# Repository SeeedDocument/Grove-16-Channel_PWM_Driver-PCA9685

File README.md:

# Grove-16-Channel_PWM_Driver-PCA9685

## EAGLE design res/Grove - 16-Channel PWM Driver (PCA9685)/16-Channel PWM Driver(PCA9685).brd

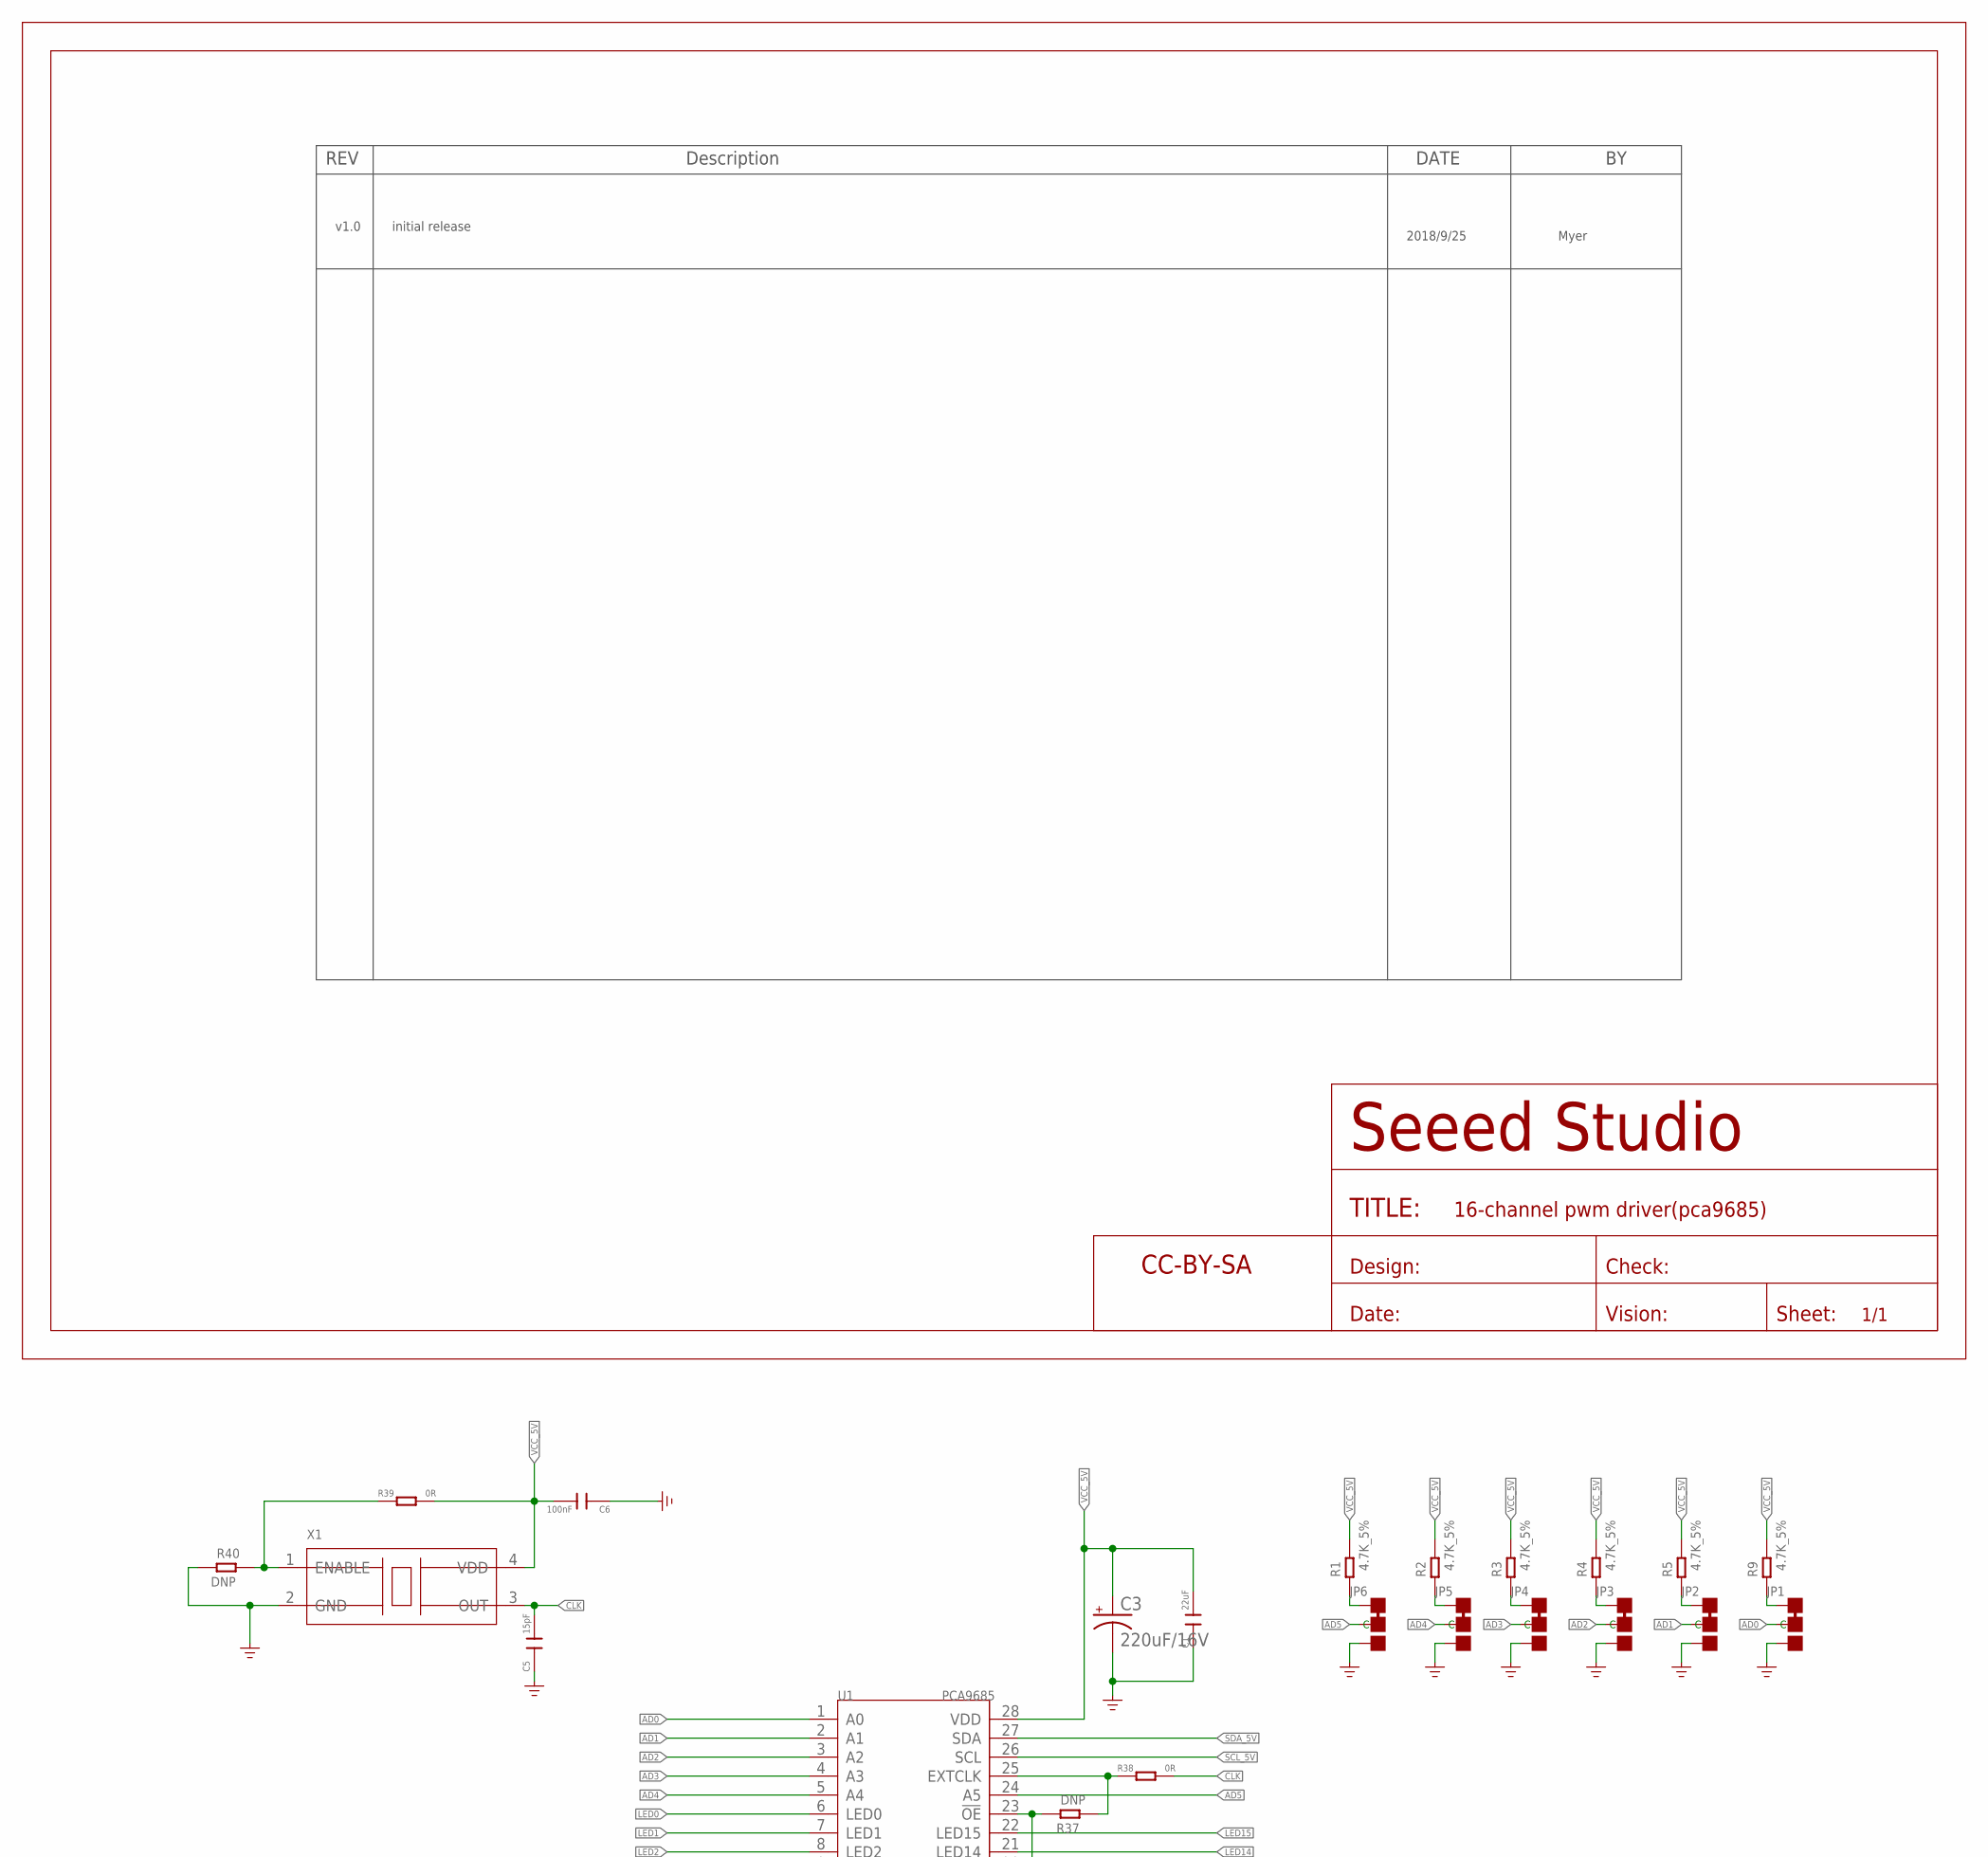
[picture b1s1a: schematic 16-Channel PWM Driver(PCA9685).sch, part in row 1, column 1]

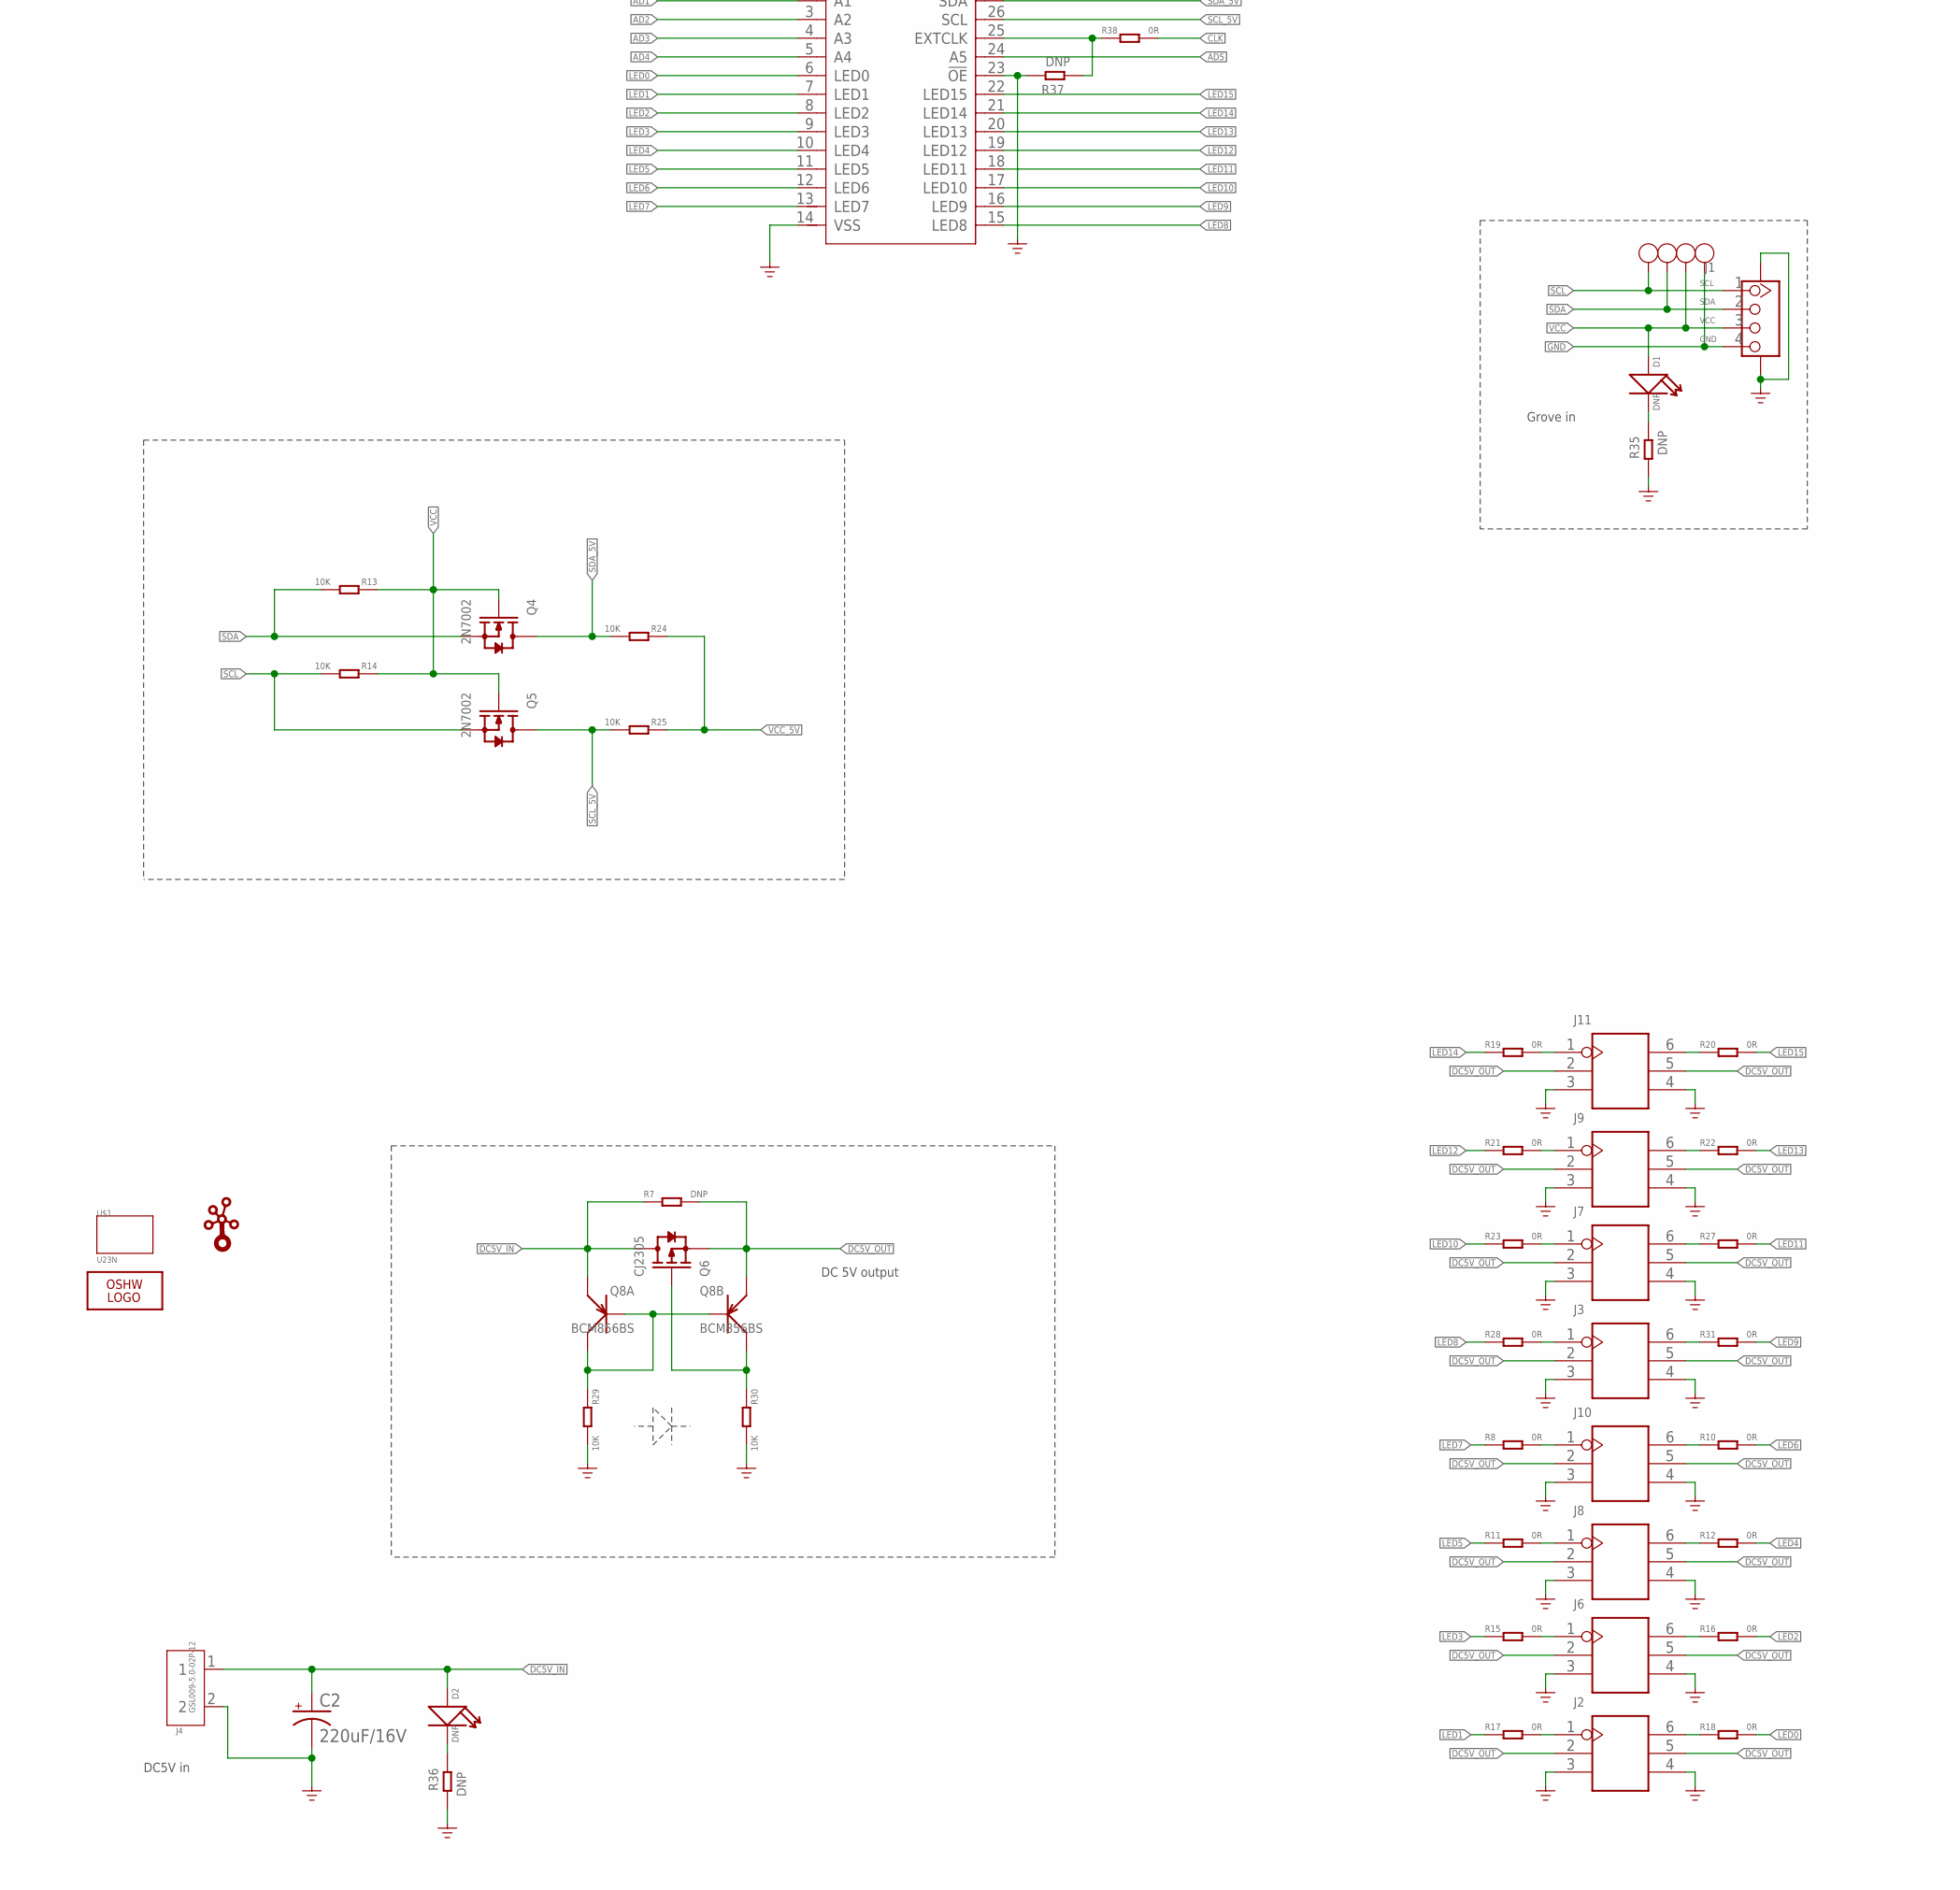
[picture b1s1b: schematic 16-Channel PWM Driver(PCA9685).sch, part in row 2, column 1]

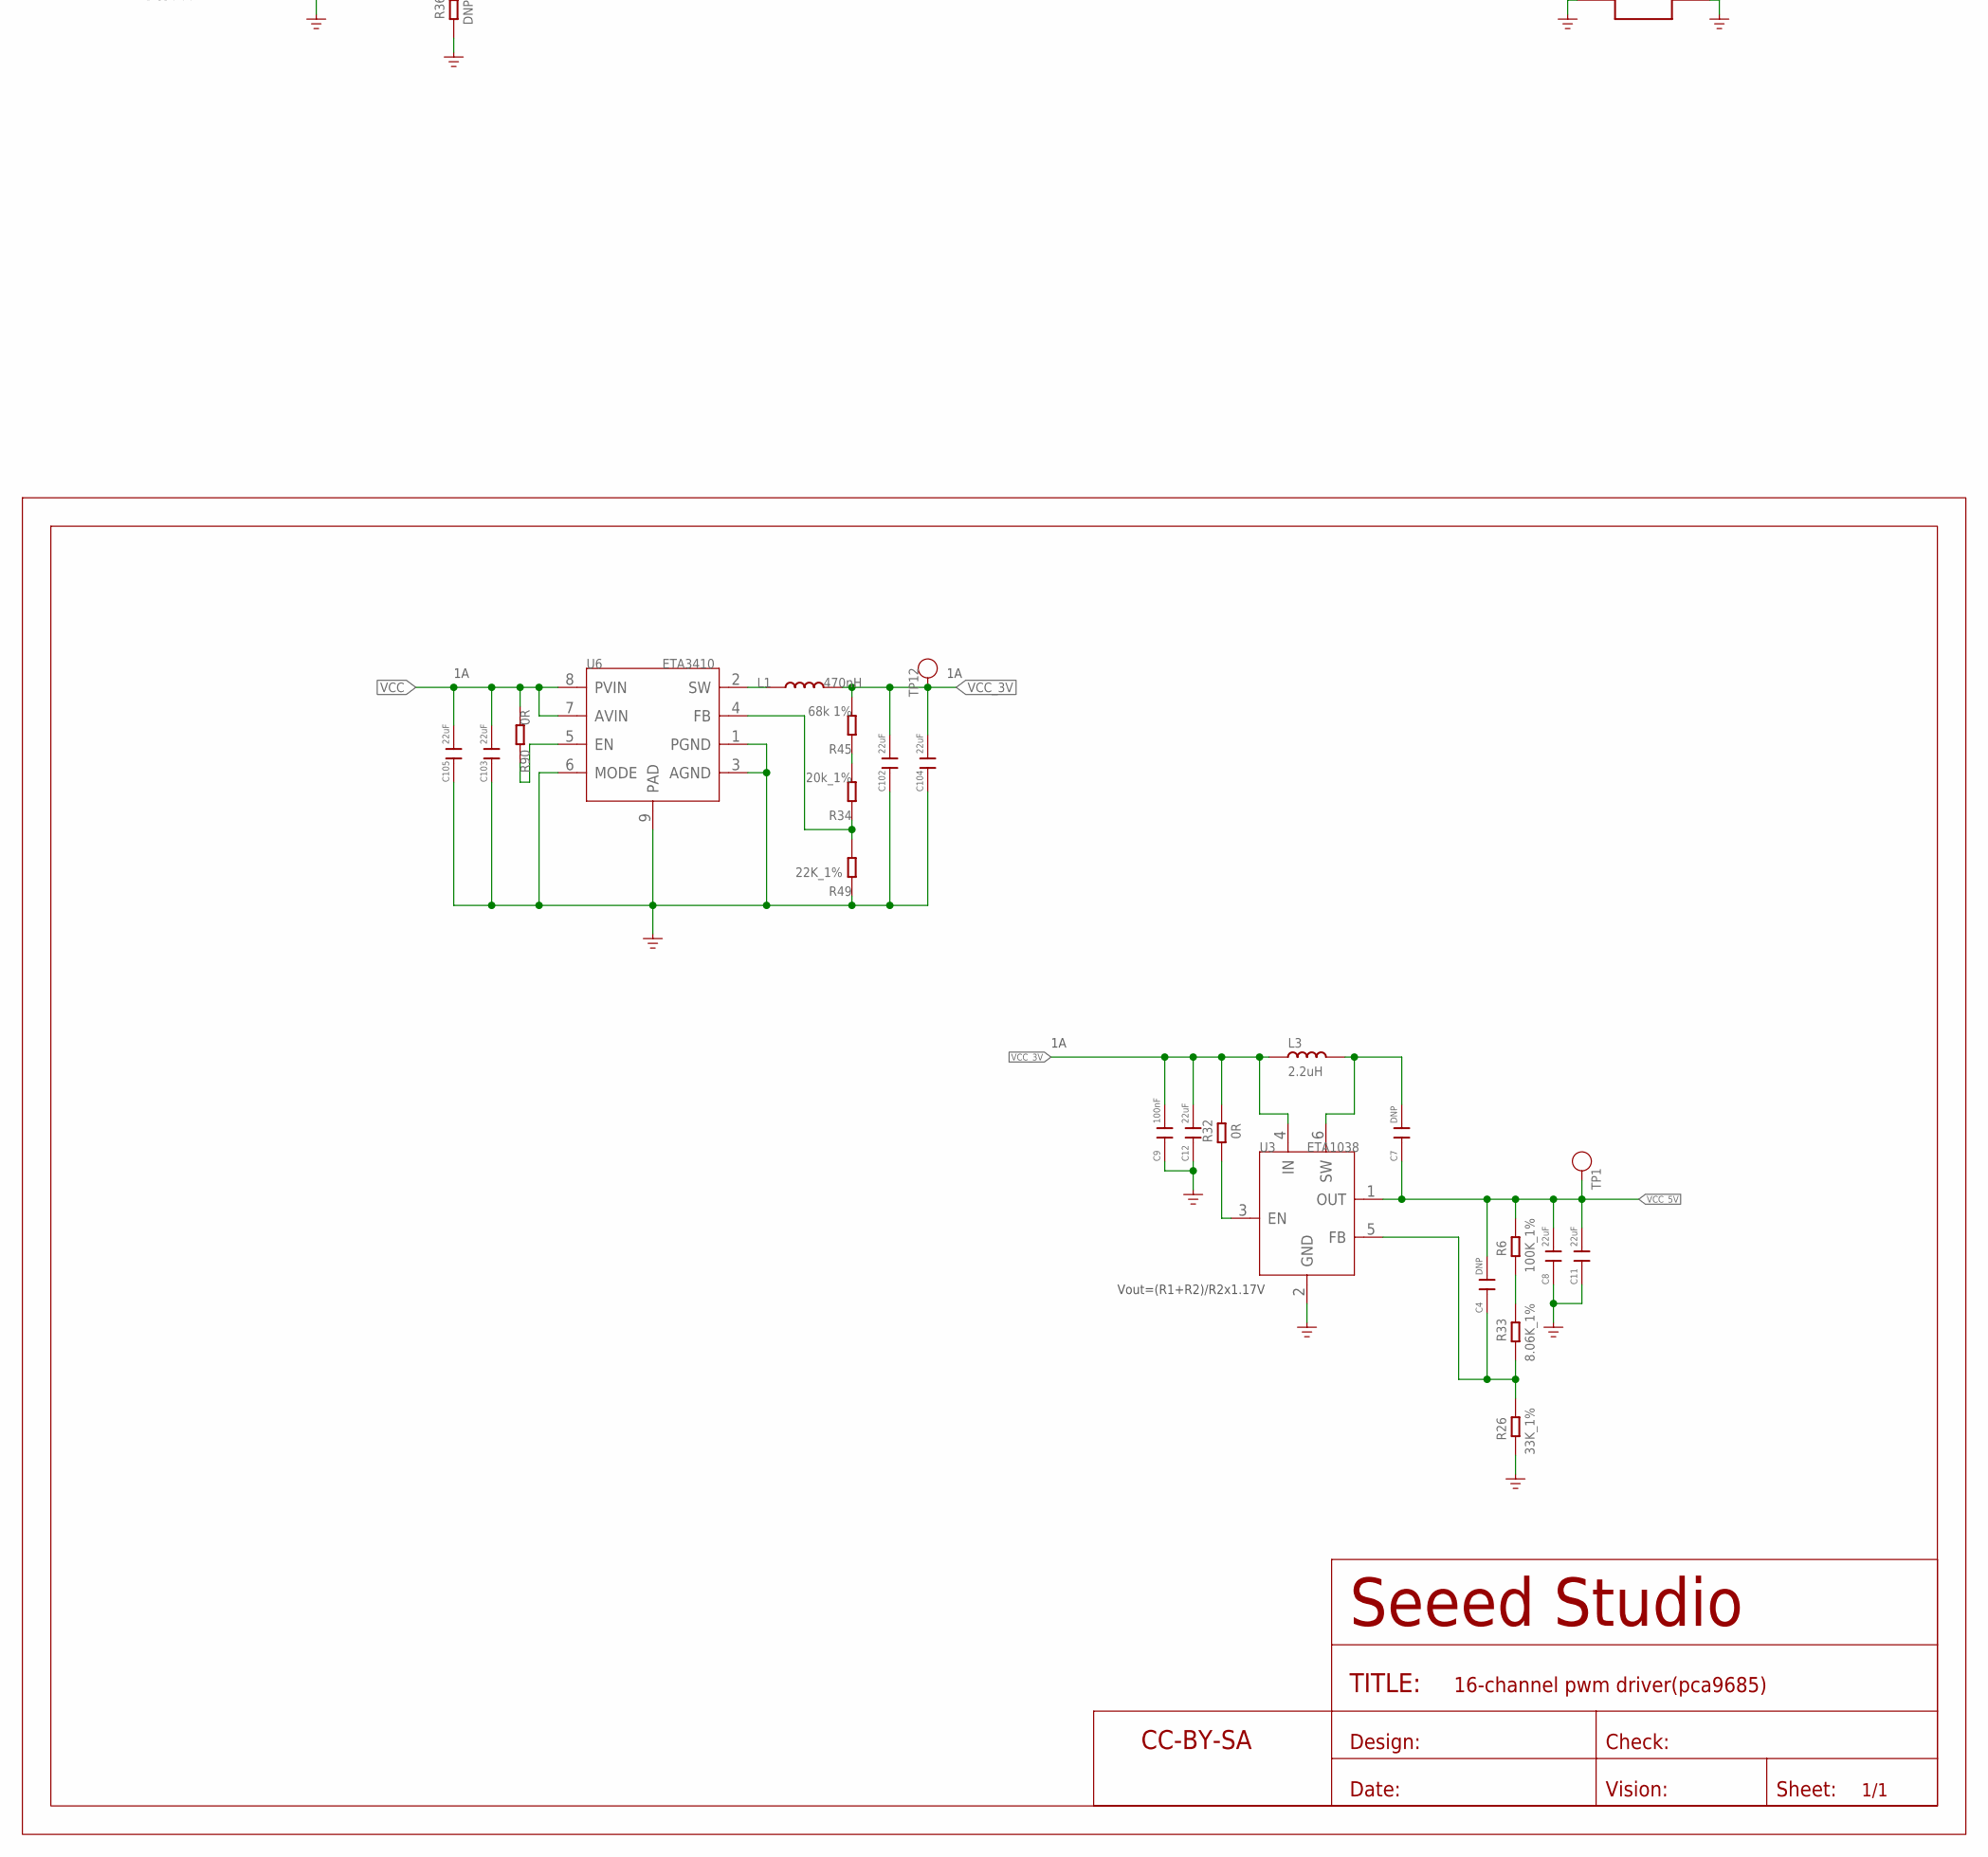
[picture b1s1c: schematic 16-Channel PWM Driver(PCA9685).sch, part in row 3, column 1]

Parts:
C1: 22uF; C0805
C2, C3: 220uF/16V; PANASONIC_D
C4, C7: DNP; C0603
C5: 15pF; C0603
C6, C9: 100nF; C0603
C8, C11, C12, C102, C103, C104, C105: 22uF; C0603
D1, D2: DNP; LED-0603
FR1, FR2: SEEEDSTUDIO-OPEN-SCH-FRAME; SEEEDSTUDIO-PCB-FRAME
GND1: TEST-POINT'4545'; TP-D45MIL
J1: GROVE-CONNECTOR-SMD'90D'; HW4-SMD-2.0-90D
J2, J3, J6, J7, J8, J9, J10, J11: HEADER-2X3P-2.54; H2X3-2.54
J4: GSL009-5.0-02P-12; 2P-5.0-10.6X10X14.8H
JP1, JP2, JP3, JP4, JP5, JP6: JP-3P-SHORT; 3P-SMD-SHORT
L1: 470nH; L201610
L3: 2.2uH; L0806
LOGO2: LOGO-OSHW-FILLX0200-NT; OSHW_FILLX200_NOTEXT
Q4, Q5: 2N7002; SOT-323
Q6: CJ2305; SOT-23
Q8: BCM856BS; SOT-363
R1, R2, R3, R4, R5, R9: 4.7K_5%; R0603
R6: 100K_1%; R0603
R7: DNP; R0805
R8, R10, R11, R12, R15, R16, R17, R18, R19, R20, R21, R22, R23, R27, R28, R31, R32, R38, R39, R90: 0R; R0603
R13, R14, R24, R25, R29, R30: 10K; R0603
R26: 33K_1%; R0603
R33: 8.06K_1%; R0603
R34: 20k_1%; R0603
R35, R36, R37, R40: DNP; R0603
R45: 68k 1%; R0603
R49: 22K_1%; R0603
SCL1: TEST-POINT'4545'; TP-D45MIL
SDA1: TEST-POINT'4545'; TP-D45MIL
TP1, TP12: TEST-POINT'4545'; TP-D45MIL
U1: PCA9685; TSSOP28-0.65-9.7X4.4X1.2MM
U3: ETA1038; SOT-23-6
U6: ETA3410; DFN8G-0.5-2X2MM
U$1: U23N; U2*3N
U$3: TWIGLOGOTWIGLOGO_SMALL; TWIGLOGO_SMALL
VCC2: TEST-POINT'4545'; TP-D45MIL
X1: CRYSTAL-OSCILLATOR'7050'; OSC4-SMD-7.0X5.0X1.0MM

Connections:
AD0: JP1.MM (C), U1.1 (A0)
AD1: JP2.MM (C), U1.2 (A1)
AD2: JP3.MM (C), U1.3 (A2)
AD3: JP4.MM (C), U1.4 (A3)
AD4: JP5.MM (C), U1.5 (A4)
AD5: JP6.MM (C), U1.24 (A5)
CLK: C5.2, R38.2, X1.3 (OUT)
DC5V_IN: C2.+, D2.+, J4.1, Q6.3 (D), Q8.1 (E), R7.1
DC5V_OUT: J2.2, J2.5, J3.2, J3.5, J6.2, J6.5, J7.2, J7.5, J8.2, J8.5, J9.2, J9.5, J10.2, J10.5, J11.2, J11.5, Q6.2 (S), Q8.4 (E), R7.2
GND: C1.1, C2.-, C3.-, C5.1, C6.1, C8.1, C9.1, C11.1, C12.1, C102.1, C103.1, C104.1, C105.1, J1.4, J1.SS1, J1.SS2, J2.3, J2.4, J3.3, J3.4, J4.2, J6.3, J6.4, J7.3, J7.4, J8.3, J8.4, J9.3, J9.4, J10.3, J10.4, J11.3, J11.4, JP1.00 (R), JP2.00 (R), JP3.00 (R), JP4.00 (R), JP5.00 (R), JP6.00 (R), R26.1, R29.2, R30.2, R35.2, R36.2, R37.1, R40.2, R49.1, SCL1.T, U1.14 (VSS), U1.23 (!OE), U3.2 (GND), U6.1 (PGND), U6.3 (AGND), U6.6 (MODE), U6.9 (PAD), X1.2 (GND)
LED0: R18.2, U1.6 (LED0)
LED1: R17.1, U1.7 (LED1)
LED2: R16.2, U1.8 (LED2)
LED3: R15.1, U1.9 (LED3)
LED4: R12.2, U1.10 (LED4)
LED5: R11.1, U1.11 (LED5)
LED6: R10.2, U1.12 (LED6)
LED7: R8.1, U1.13 (LED7)
LED8: R28.1, U1.15 (LED8)
LED9: R31.2, U1.16 (LED9)
LED10: R23.1, U1.17 (LED10)
LED11: R27.2, U1.18 (LED11)
LED12: R21.1, U1.19 (LED12)
LED13: R22.2, U1.20 (LED13)
LED14: R19.1, U1.21 (LED14)
LED15: R20.2, U1.22 (LED15)
unnamed: JP1.11 (L), R9.2
unnamed: J3.1, R28.2
unnamed: J11.1, R19.2
unnamed: JP2.11 (L), R5.2
unnamed: JP3.11 (L), R4.2
unnamed: JP4.11 (L), R3.2
unnamed: JP5.11 (L), R2.2
unnamed: JP6.11 (L), R1.2
unnamed: J11.6, R20.1
unnamed: J3.6, R31.1
unnamed: J8.1, R11.2
unnamed: J8.6, R12.1
unnamed: J6.1, R15.2
unnamed: J6.6, R16.1
unnamed: J2.1, R17.2
unnamed: Q8.2 (B), Q8.5 (B), Q8.6 (C), R29.1
unnamed: J2.6, R18.1
unnamed: Q6.1 (G), Q8.3 (C), R30.1
unnamed: J9.1, R21.2
unnamed: J9.6, R22.1
unnamed: J7.1, R23.2
unnamed: J7.6, R27.1
unnamed: J10.1, R8.2
unnamed: J10.6, R10.1
unnamed: R37.2, R38.1, U1.25 (EXTCLK)
unnamed: L1.1, U6.2 (SW)
unnamed: R90.1, U6.5 (EN)
unnamed: C7.2, L3.2, U3.6 (SW)
unnamed: C4.1, R26.2, R33.2, U3.5 (FB)
unnamed: R32.2, U3.3 (EN)
unnamed: R6.2, R33.1
unnamed: R34.2, R45.1
unnamed: D1.-, R35.1
unnamed: D2.-, R36.1
unnamed: R39.1, R40.1, X1.1 (ENABLE)
unnamed: R34.1, R49.2, U6.4 (FB)
SCL: GND1.T, J1.1, Q5.2 (S), R14.2
SCL_5V: Q5.3 (D), R25.2, U1.26 (SCL)
SDA: J1.2, Q4.2 (S), R13.2, VCC2.T
SDA_5V: Q4.3 (D), R24.2, U1.27 (SDA)
VCC: C103.2, C105.2, D1.+, J1.3, Q4.1 (G), Q5.1 (G), R13.1, R14.1, R90.2, SDA1.T, U6.7 (AVIN), U6.8 (PVIN)
VCC_3V: C9.2, C12.2, C102.2, C104.2, L1.2, L3.1, R32.1, R45.2, TP12.T, U3.4 (IN)
VCC_5V: C1.2, C3.+, C4.2, C6.2, C7.1, C8.2, C11.2, R1.1, R2.1, R3.1, R4.1, R5.1, R6.1, R9.1, R24.1, R25.1, R39.2, TP1.T, U1.28 (VDD), U3.1 (OUT), X1.4 (VDD)

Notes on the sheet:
Grove in
v1.0
initial release
2018/9/25
Myer
DC 5V output
Vout=(R1+R2)/R2x1.17V
DC5V in

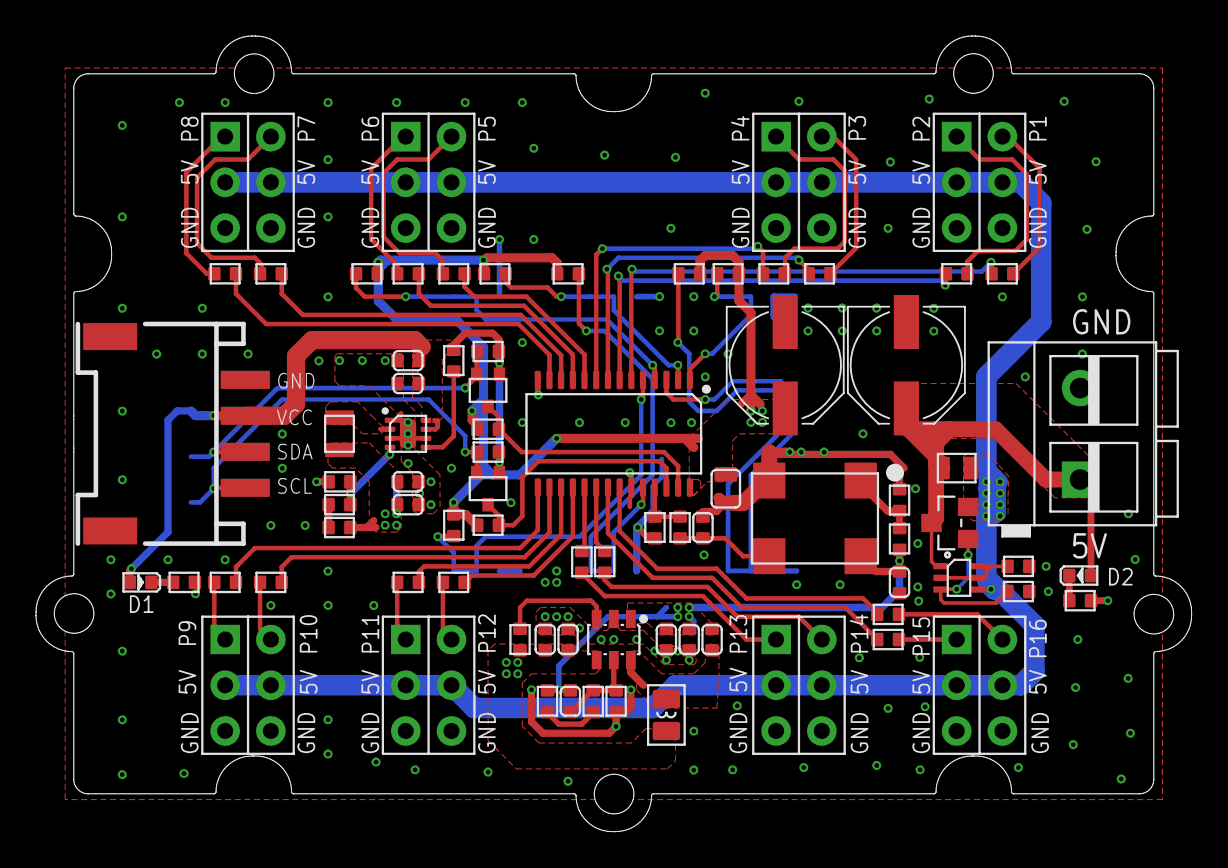
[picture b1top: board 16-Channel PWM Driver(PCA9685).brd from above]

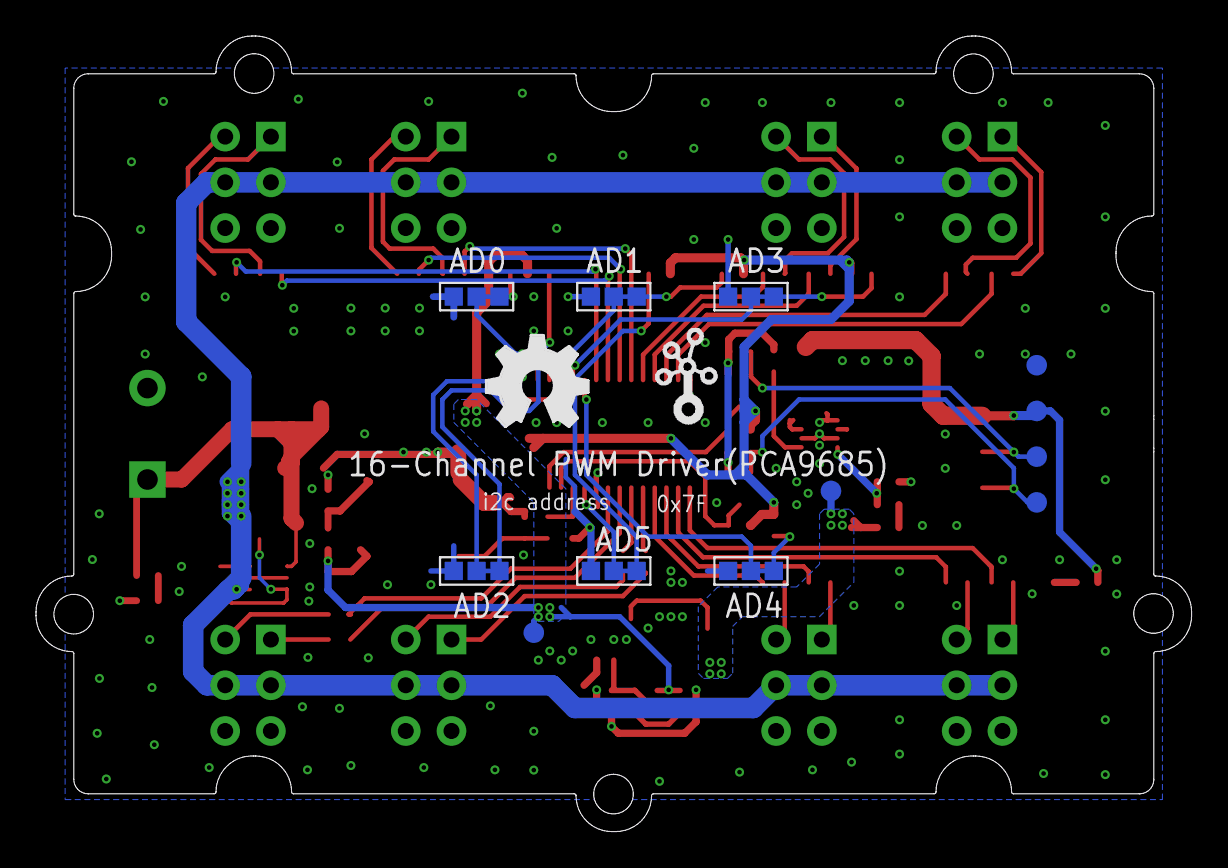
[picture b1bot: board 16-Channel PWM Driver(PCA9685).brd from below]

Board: 2 copper layers, 64.2 x 44.2 mm, 97 parts (14 on the bottom side), 69 nets.

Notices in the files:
parts and their libraries:
moudle-new: This work is licensed under the Creative Commons Attribution 4.0 International License.
To view a copy of this license,visit:
http://creativecommons.org/licenses/by-sa/4.0
moudle-new: CC-BY-SA
